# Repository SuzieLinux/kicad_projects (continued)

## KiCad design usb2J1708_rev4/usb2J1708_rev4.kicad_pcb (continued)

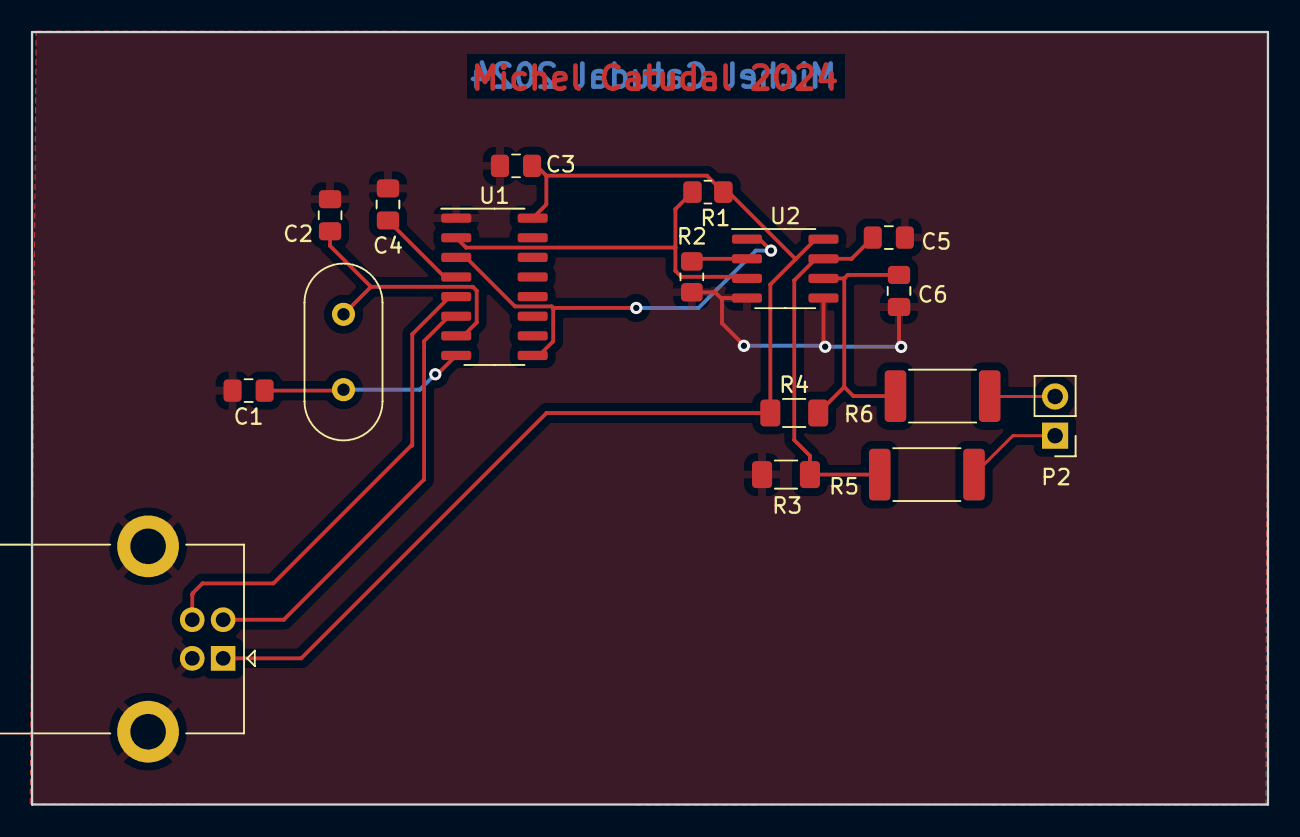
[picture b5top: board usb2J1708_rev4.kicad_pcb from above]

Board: 2 copper layers, 80.0 x 50.0 mm, 17 parts (0 on the bottom side), 14 nets.

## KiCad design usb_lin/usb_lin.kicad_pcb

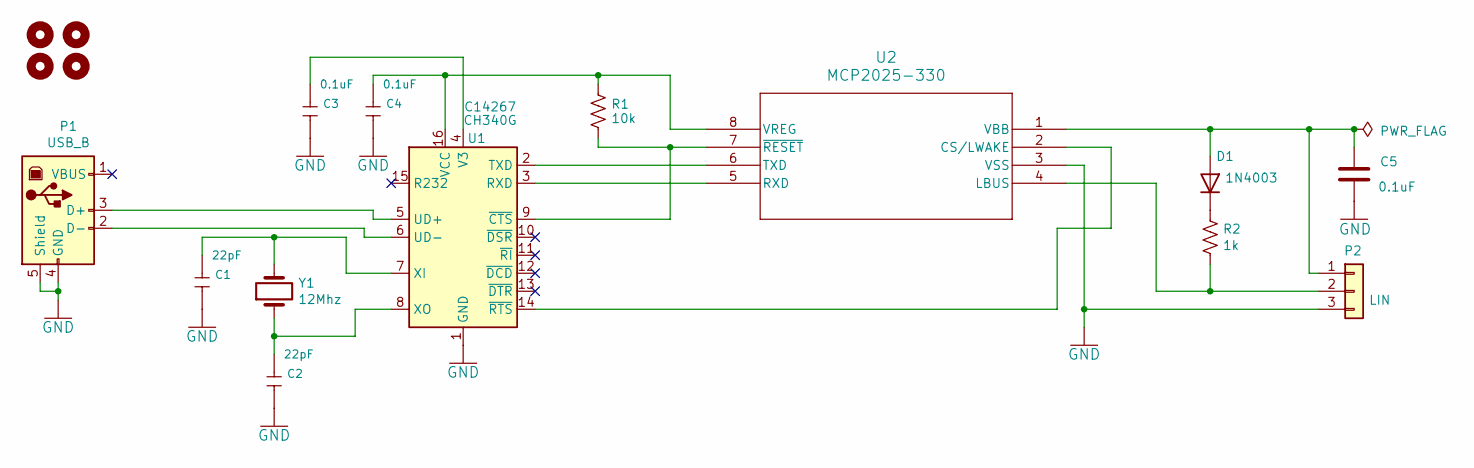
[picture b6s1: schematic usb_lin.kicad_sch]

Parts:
C1, C2: 22pF; C_0805_2012Metric_Pad1.18x1.45mm_HandSolder; MPN CC0603KRX7R9BB104; LCSC C1562
C3, C4: 0.1uF; C_0805_2012Metric_Pad1.18x1.45mm_HandSolder; MPN CC0603KRX7R9BB104; LCSC C14663
C5: 0.1uF; C_0805_2012Metric_Pad1.18x1.45mm_HandSolder
D1: 1N4003; D_A-405_P10.16mm_Horizontal
H5, H6, H7, H8: MountingHole; MountingHole_2.7mm_M2.5_DIN965_Pad
P1: USB_B; USB_B_OST_USB-B1HSxx_Horizontal
P2: LIN; PinHeader_1x03_P2.54mm_Vertical
R1: 10k; R_0805_2012Metric_Pad1.20x1.40mm_HandSolder
R2: 1k; R_1206_3216Metric_Pad1.30x1.75mm_HandSolder
U1: CH340G; SOIC-16_3.9x9.9mm_P1.27mm; LCSC C14267
U2: MCP2025-330; SOIC8_4P9X3P9MC_MCH
Y1: 12Mhz; Crystal_HC49-4H_Vertical

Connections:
GND: C1.2, C2.2, C3.2, C4.2, C5.2, P1.4 (GND), P1.5 (Shield), P2.3, U1.1 (GND), U2.3 (VSS)
unnamed: C5.1, D1.2 (A), P2.1, U2.1 (VBB)
unnamed: D1.1 (K), R2.1
unnamed: P1.3 (D+), U1.5 (UD+)
unnamed: P1.2 (D-), U1.6 (UD-)
unnamed: P2.2, R2.2, U2.4 (LBUS)
unnamed: U1.3 (RXD), U2.5 (RXD)
unnamed: U1.2 (TXD), U2.6 (TXD)
unnamed: C3.1, U1.4 (V3)
unnamed: C4.1, R1.1, U1.16 (VCC), U2.8 (VREG)
unnamed: C1.1, U1.7 (XI), Y1.2
unnamed: C2.1, U1.8 (XO), Y1.1
unnamed: R1.2, U1.9 (~CTS), U2.7 (~RESET)
unnamed: U1.14 (~RTS), U2.2 (CS/LWAKE)

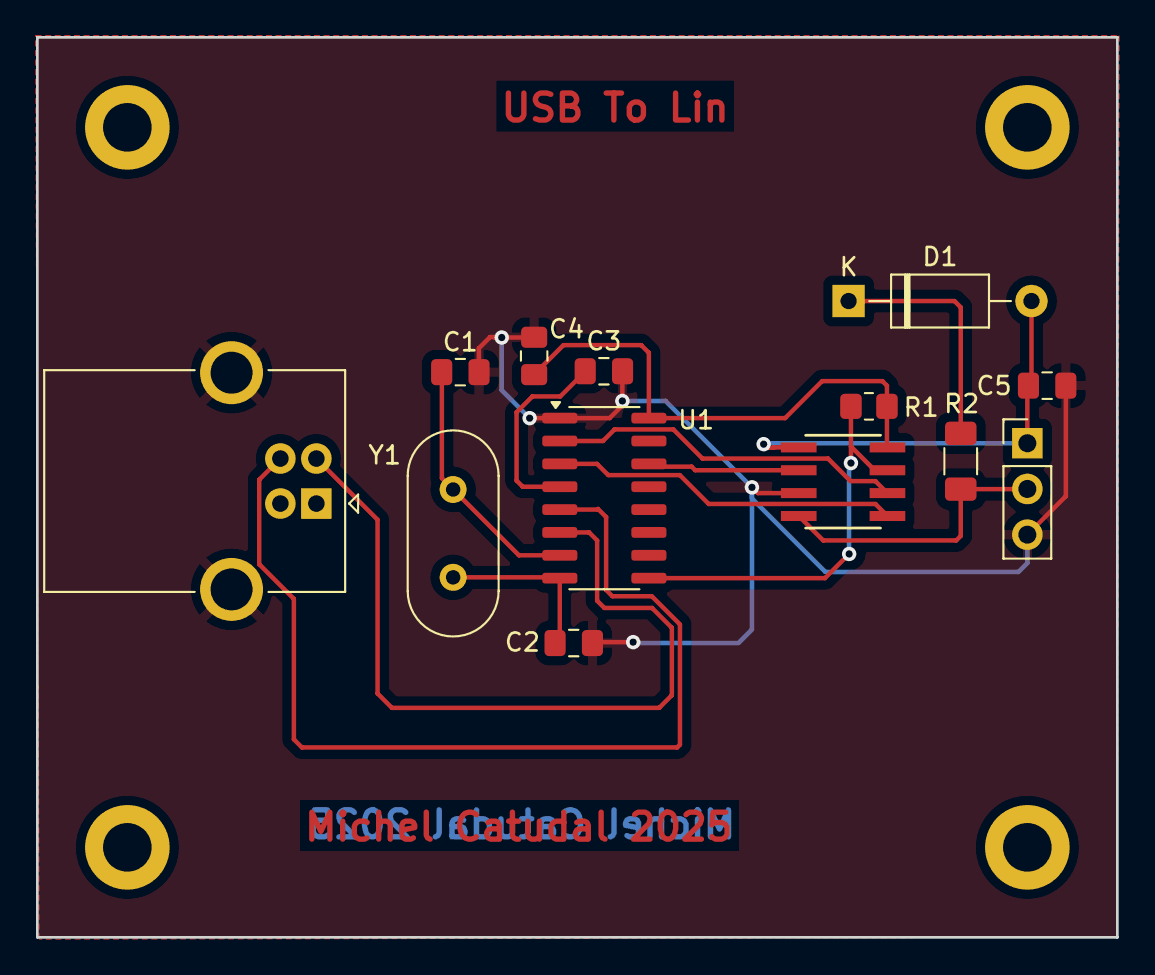
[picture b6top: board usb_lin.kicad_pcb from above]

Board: 2 copper layers, 60.0 x 50.0 mm, 17 parts (0 on the bottom side), 14 nets.

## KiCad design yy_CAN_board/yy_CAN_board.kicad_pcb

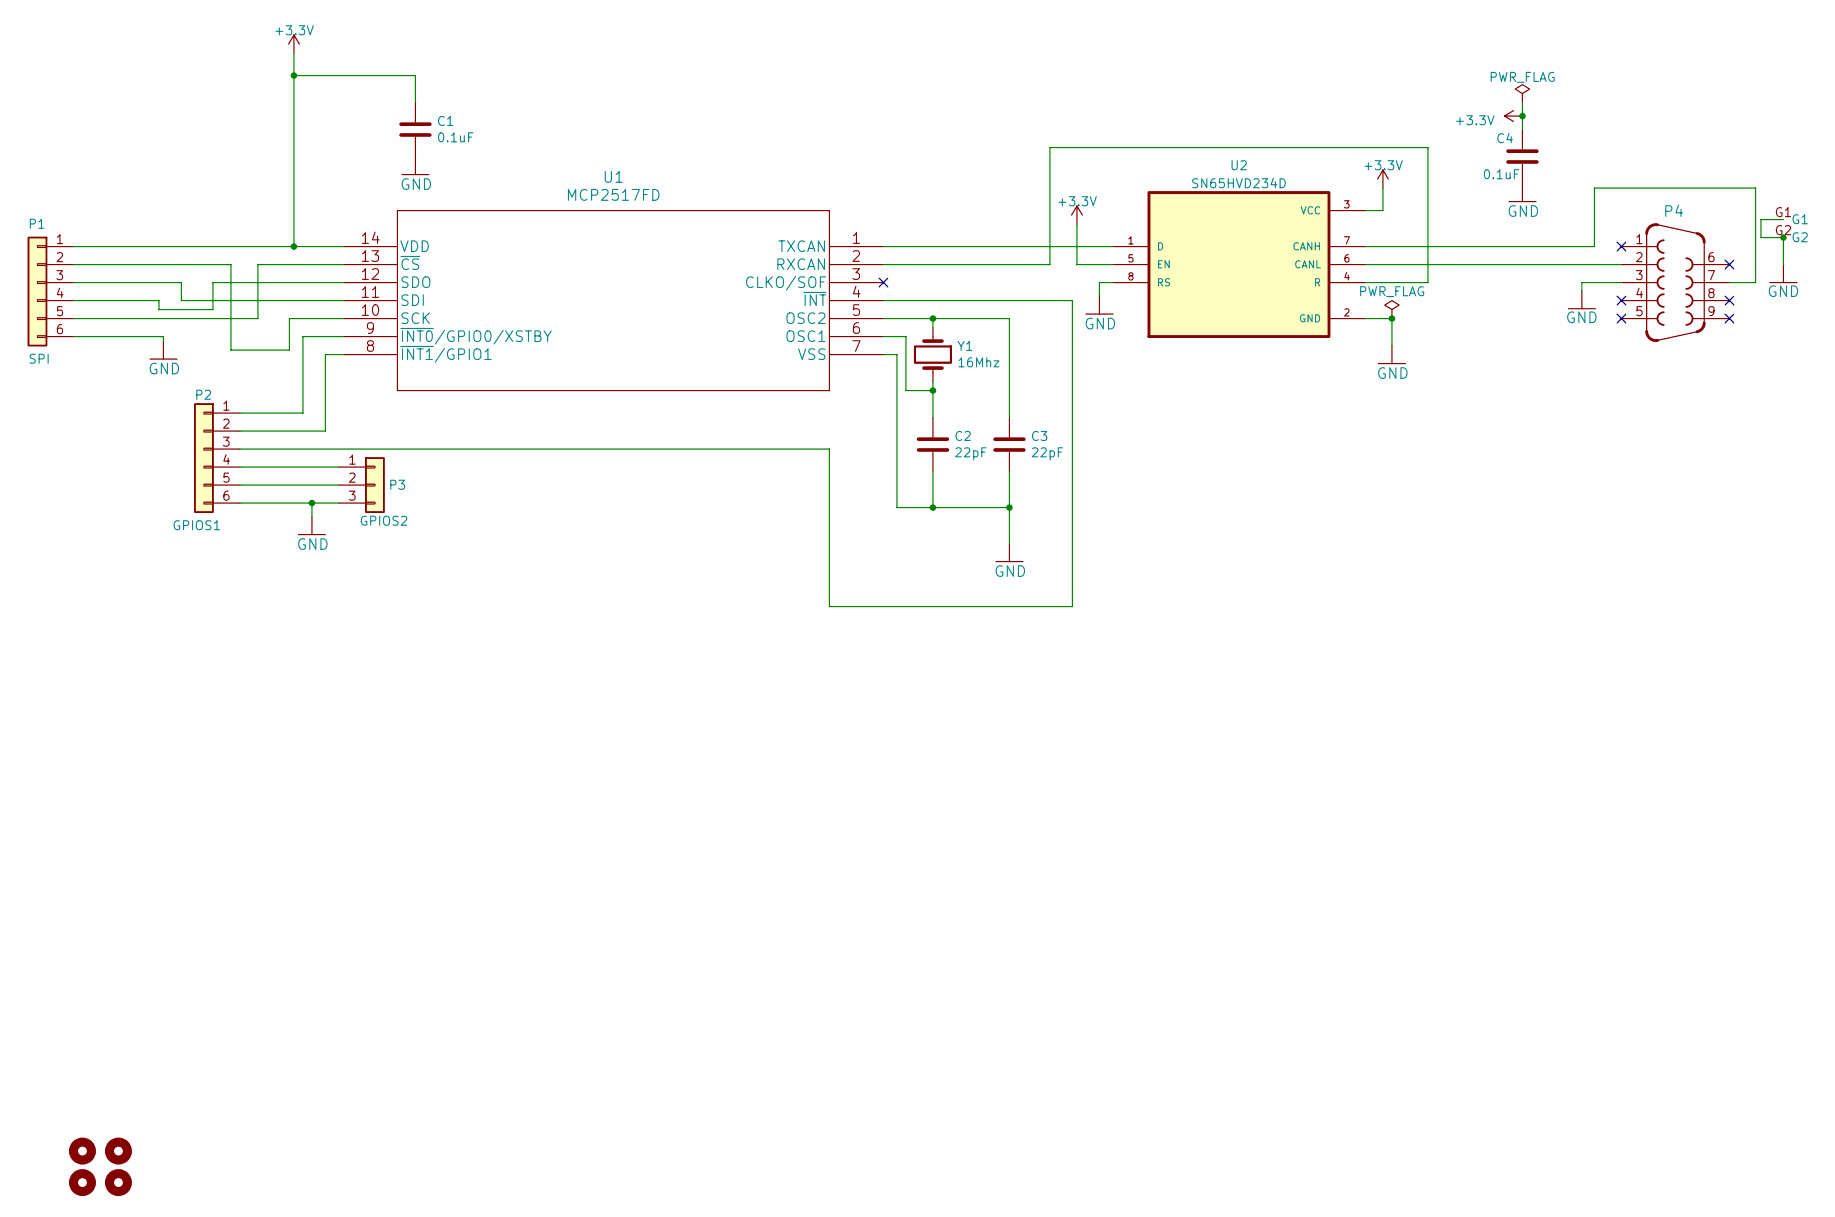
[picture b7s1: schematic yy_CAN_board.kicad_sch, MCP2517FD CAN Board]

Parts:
C1, C4: 0.1uF; C_0805_2012Metric_Pad1.18x1.45mm_HandSolder
C2, C3: 22pF; C_0805_2012Metric_Pad1.18x1.45mm_HandSolder
H1, H2, H3, H4: MountingHole; MountingHole_2.7mm_M2.5_DIN965_Pad
P1: SPI; JST_PH_B6B-PH-SM4-TB_1x06-1MP_P2.00mm_Vertical
P2: GPIOS1; JST_PH_B6B-PH-SM4-TB_1x06-1MP_P2.00mm_Vertical
P3: GPIOS2; JST_PH_B3B-PH-SM4-TB_1x03-1MP_P2.00mm_Vertical
P4: F09HP
U1: MCP2517FD; MCP2518FD
U2: SN65HVD234D; SOIC127P599X175-8N
Y1: 16Mhz; Crystal_HC49-4H_Vertical

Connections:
+3.3V: C1.1, C4.1, P1.1, U1.14 (VDD), U2.3 (VCC), U2.5 (EN)
GND: C1.2, C2.2, C3.2, C4.2, P1.6, P1.MP, P2.6, P2.MP, P3.3, P3.MP, P4.3, P4.G1, P4.G2, U1.7 (VSS), U2.2 (GND), U2.8 (RS)
unnamed: P1.2, U1.10 (SCK)
unnamed: P1.3, U1.11 (SDI)
unnamed: P1.4, U1.12 (SDO)
unnamed: P1.5, U1.13 (~CS)
unnamed: P2.1, U1.9 (~INT0/GPIO0/XSTBY)
unnamed: P2.2, U1.8 (~INT1/GPIO1)
unnamed: P2.3, U1.4 (~INT)
unnamed: P2.4, P3.1
unnamed: P2.5, P3.2
unnamed: C2.1, U1.6 (OSC1), Y1.2
unnamed: C3.1, U1.5 (OSC2), Y1.1
unnamed: U1.2 (RXCAN), U2.4 (R)
unnamed: U1.1 (TXCAN), U2.1 (D)
unnamed: P4.7, U2.7 (CANH)
unnamed: P4.2, U2.6 (CANL)

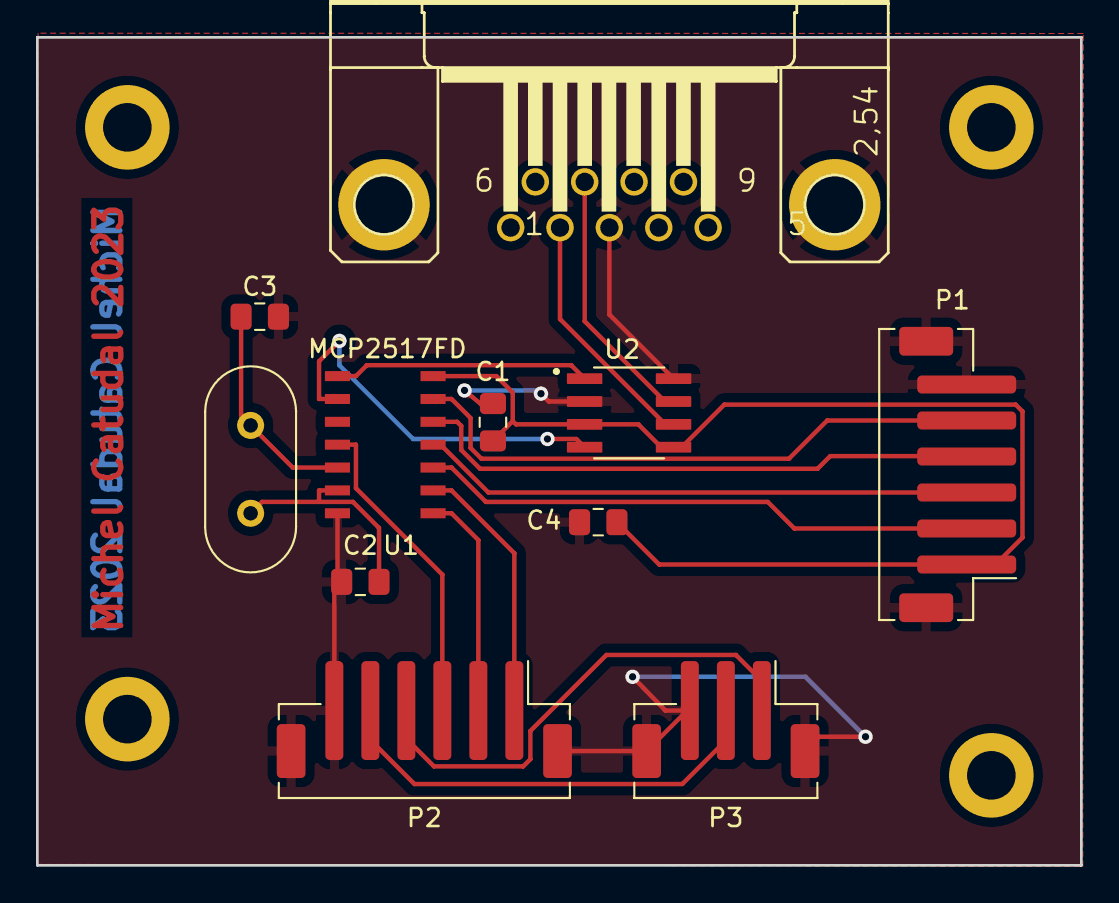
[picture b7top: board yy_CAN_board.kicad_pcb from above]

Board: 2 copper layers, 58.0 x 46.0 mm, 15 parts (0 on the bottom side), 17 nets.
